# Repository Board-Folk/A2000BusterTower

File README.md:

# A2000BusterTower
 Amiga A2000 Buster Tower Recreation PCB

 I take no responsibility for any damaged caused by using this PCB. Use at your own risk.

 Currently Untested

 Thanks to PeepoUK for the original PCB layout,
 and to LIV2 for working out the PAL Logic and board layout.

The code is written for the GAL16V8 as a replacement of the original PAL Chip

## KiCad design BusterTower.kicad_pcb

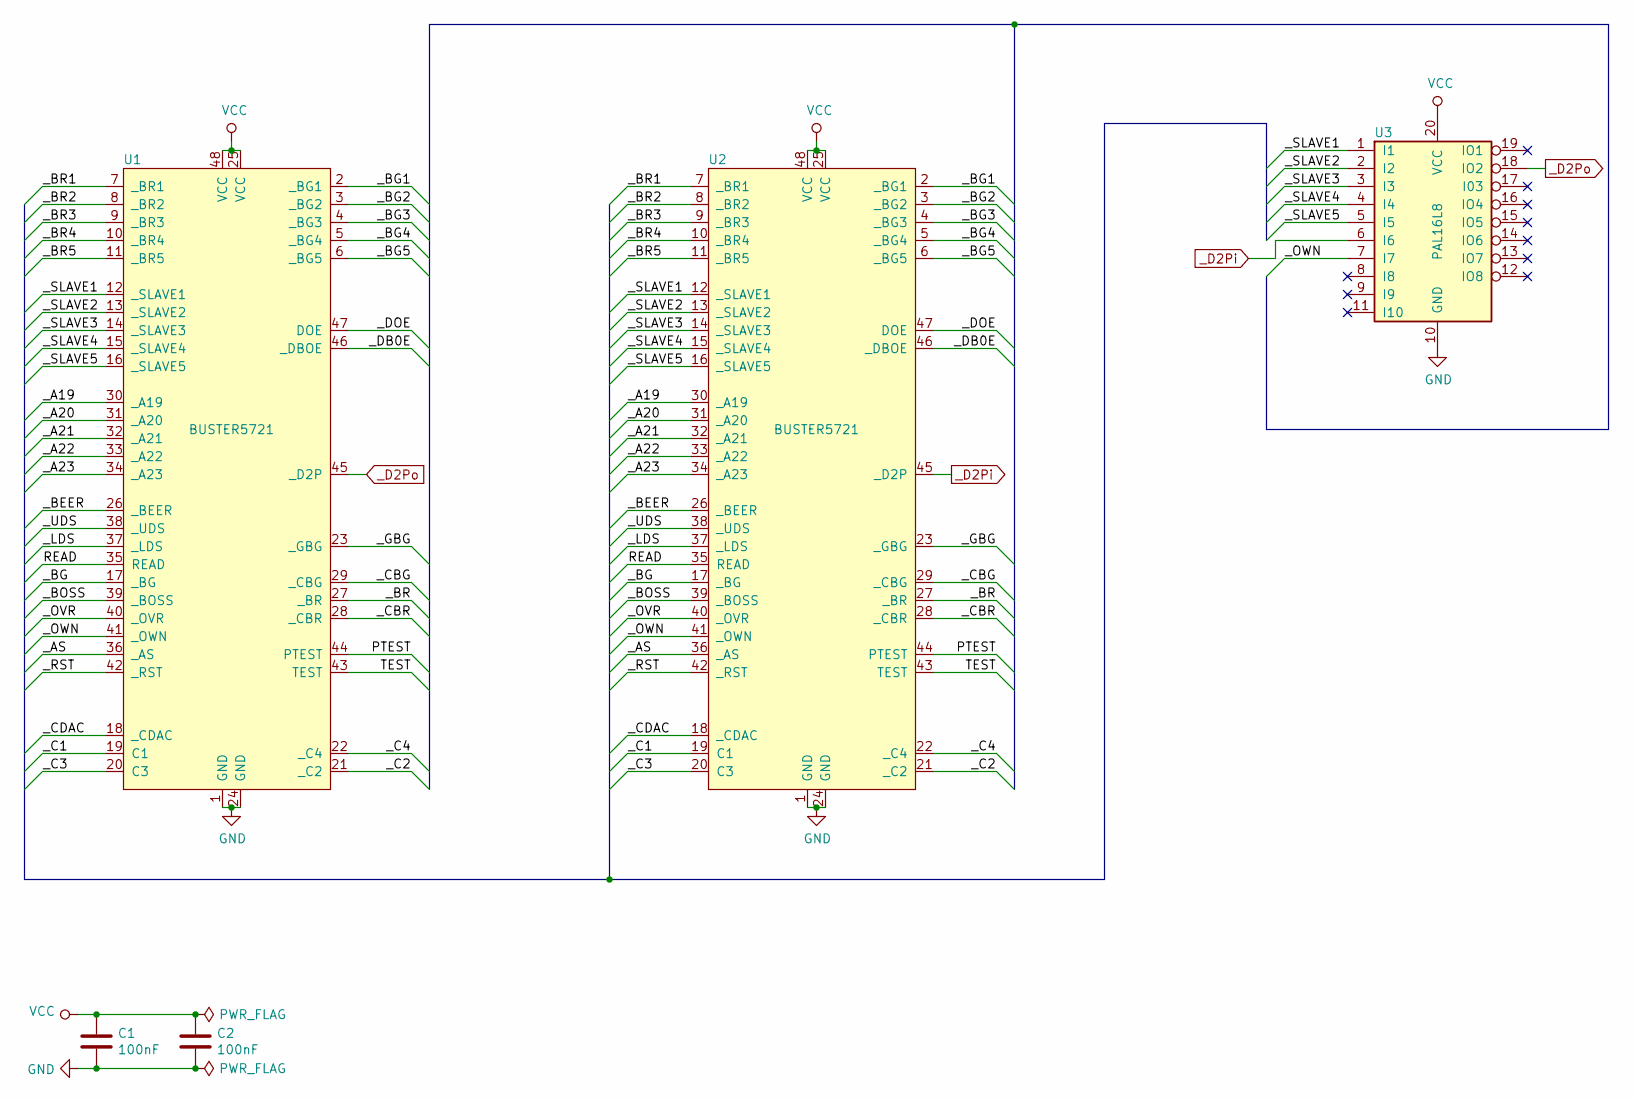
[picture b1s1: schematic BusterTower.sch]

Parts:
C1, C2: 100nF; C_Disc_D10.0mm_W2.5mm_P5.00mm
U1, U2: BUSTER5721; DIP-48_W15.24mm_Socket
U3: PAL16L8; DIP-20_W7.62mm_Socket

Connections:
/PTEST: U1.44 (PTEST), U2.44 (PTEST)
/READ: U1.35 (READ), U2.35 (READ)
/TEST: U1.43 (TEST), U2.43 (TEST)
/_A19: U1.30 (_A19), U2.30 (_A19)
/_A20: U1.31 (_A20), U2.31 (_A20)
/_A21: U1.32 (_A21), U2.32 (_A21)
/_A22: U1.33 (_A22), U2.33 (_A22)
/_A23: U1.34 (_A23), U2.34 (_A23)
/_AS: U1.36 (_AS), U2.36 (_AS)
/_BEER: U1.26 (_BEER), U2.26 (_BEER)
/_BG: U1.17 (_BG), U2.17 (_BG)
/_BG1: U1.2 (_BG1), U2.2 (_BG1)
/_BG2: U1.3 (_BG2), U2.3 (_BG2)
/_BG3: U1.4 (_BG3), U2.4 (_BG3)
/_BG4: U1.5 (_BG4), U2.5 (_BG4)
/_BG5: U1.6 (_BG5), U2.6 (_BG5)
/_BOSS: U1.39 (_BOSS), U2.39 (_BOSS)
/_BR: U1.27 (_BR), U2.27 (_BR)
/_BR1: U1.7 (_BR1), U2.7 (_BR1)
/_BR2: U1.8 (_BR2), U2.8 (_BR2)
/_BR3: U1.9 (_BR3), U2.9 (_BR3)
/_BR4: U1.10 (_BR4), U2.10 (_BR4)
/_BR5: U1.11 (_BR5), U2.11 (_BR5)
/_C1: U1.19 (C1), U2.19 (C1)
/_C2: U1.21 (_C2), U2.21 (_C2)
/_C3: U1.20 (C3), U2.20 (C3)
/_C4: U1.22 (_C4), U2.22 (_C4)
/_CBG: U1.29 (_CBG), U2.29 (_CBG)
/_CBR: U1.28 (_CBR), U2.28 (_CBR)
/_CDAC: U1.18 (_CDAC), U2.18 (_CDAC)
/_DB0E: U1.46 (_DBOE), U2.46 (_DBOE)
/_DOE: U1.47 (DOE), U2.47 (DOE)
/_GBG: U1.23 (_GBG), U2.23 (_GBG)
/_LDS: U1.37 (_LDS), U2.37 (_LDS)
/_OVR: U1.40 (_OVR), U2.40 (_OVR)
/_OWN: U1.41 (_OWN), U2.41 (_OWN), U3.7 (I7)
/_RST: U1.42 (_RST), U2.42 (_RST)
/_SLAVE1: U1.12 (_SLAVE1), U2.12 (_SLAVE1), U3.1 (I1)
/_SLAVE2: U1.13 (_SLAVE2), U2.13 (_SLAVE2), U3.2 (I2)
/_SLAVE3: U1.14 (_SLAVE3), U2.14 (_SLAVE3), U3.3 (I3)
/_SLAVE4: U1.15 (_SLAVE4), U2.15 (_SLAVE4), U3.4 (I4)
/_SLAVE5: U1.16 (_SLAVE5), U2.16 (_SLAVE5), U3.5 (I5)
/_UDS: U1.38 (_UDS), U2.38 (_UDS)
GND: C1.2, C2.2, U1.1 (GND), U1.24 (GND), U2.1 (GND), U2.24 (GND), U3.10 (GND)
VCC: C1.1, C2.1, U1.25 (VCC), U1.48 (VCC), U2.25 (VCC), U2.48 (VCC), U3.20 (VCC)
_D2Pi: U2.45 (_D2P), U3.6 (I6)
_D2Po: U1.45 (_D2P), U3.18 (IO2)

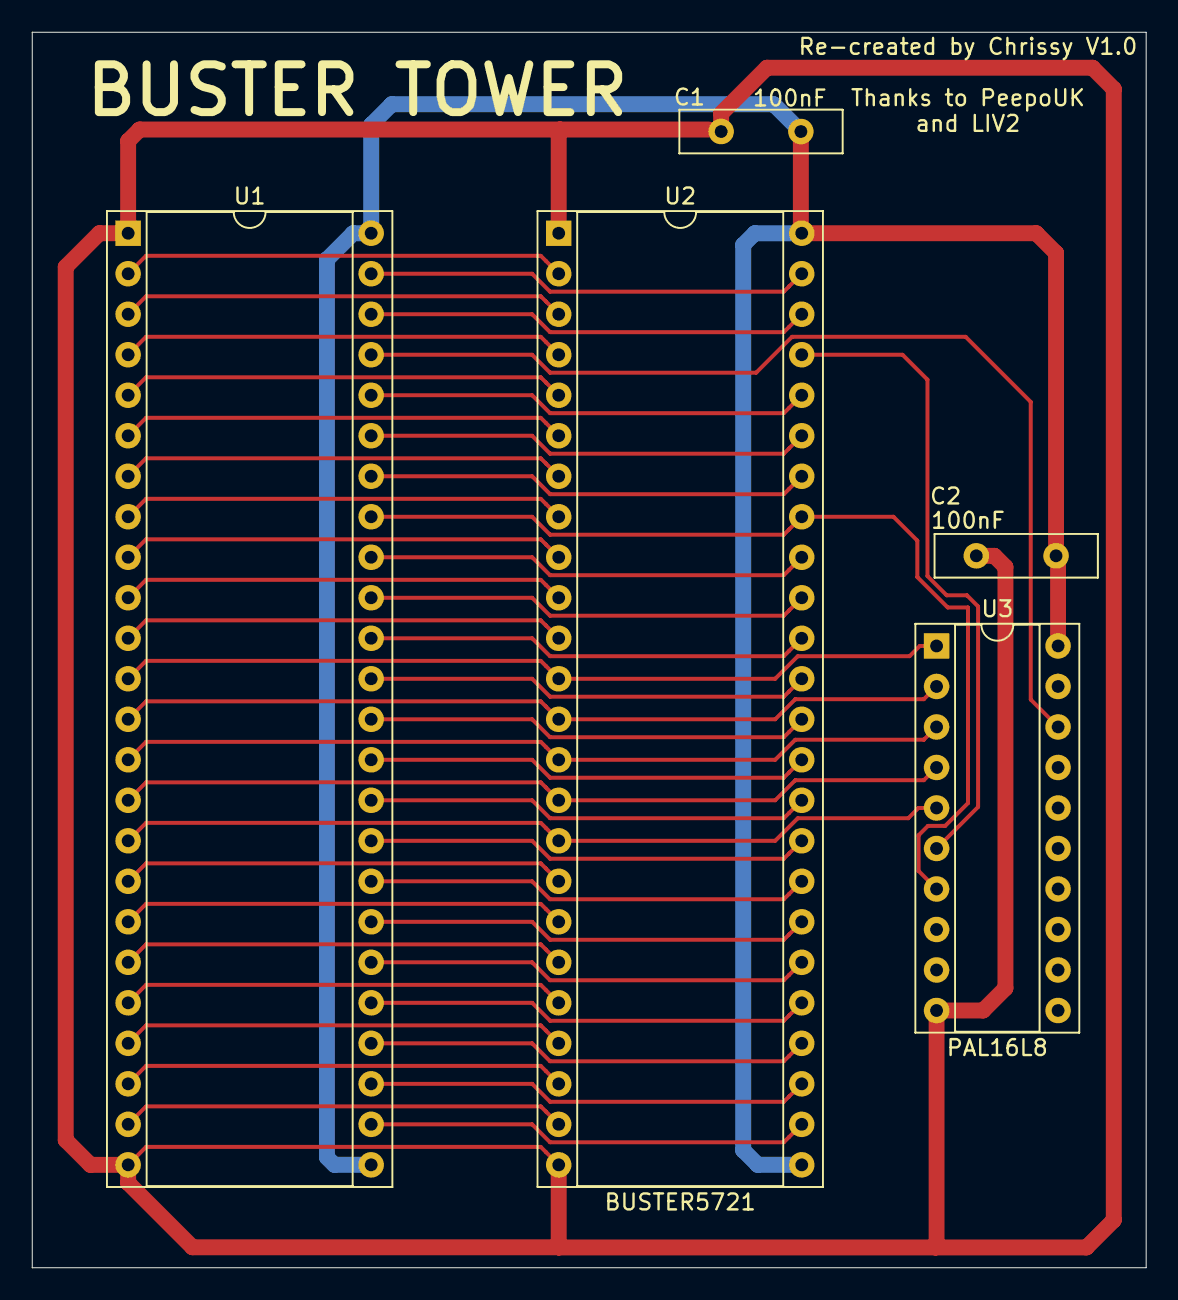
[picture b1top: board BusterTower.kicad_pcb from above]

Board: 2 copper layers, 69.8 x 77.5 mm, 5 parts (0 on the bottom side), 47 nets.

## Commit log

2020-08-21 Added gerbers
2020-09-23 PAL LOGIC
    Added PAL Logic
